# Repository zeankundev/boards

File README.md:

# zeankun.dev's KiCad Boards Repository
A collection of folders for all of my KiCad projects. Archived projects also go here. Go take a look if you want to explore

## Prerequisite
You will need:
- KiCad 8.0 (do not use nightly builds) or later
- git

Just clone the repo. That's it.
```
git clone https://github.com/zeankundev/boards.git
```

## Directory explanation
Most of the projects you see here often orientate around microcontrollers. If you want an even more detailed one, you can read the listing here.

- `Pico2040` and `Pico2350` series. These are my self-designed boards oriented mostly around ARM microcontrollers. especially the RP2040 and the RP2350
- `LiPower`, `BreadPower` and `LCDRucksack`. Those are two board categories that I like to classify them as being "useless". LiPower being the overengineered version of the TP4056 charger, BreadPower being the most **generic** breadboard power supply. Of course, this was designed before I even know USB-C PD. LCDRucksack is just literally a clone of the LCD backpacks out there, but with castellated holes.
- `ProyekOPSI2023` was the board I designed for the Indonesian research competition OPSI, in which I participated. There are two variants; the main is one contains an integrated MCU, being the ATMega328P, while the other one requires you to solder on a Pico2040 R2 Wireless by yourself.

Have fun, LOL. Dig in on my archive. I might try to update more if I have a board to design. Anyways, cya.

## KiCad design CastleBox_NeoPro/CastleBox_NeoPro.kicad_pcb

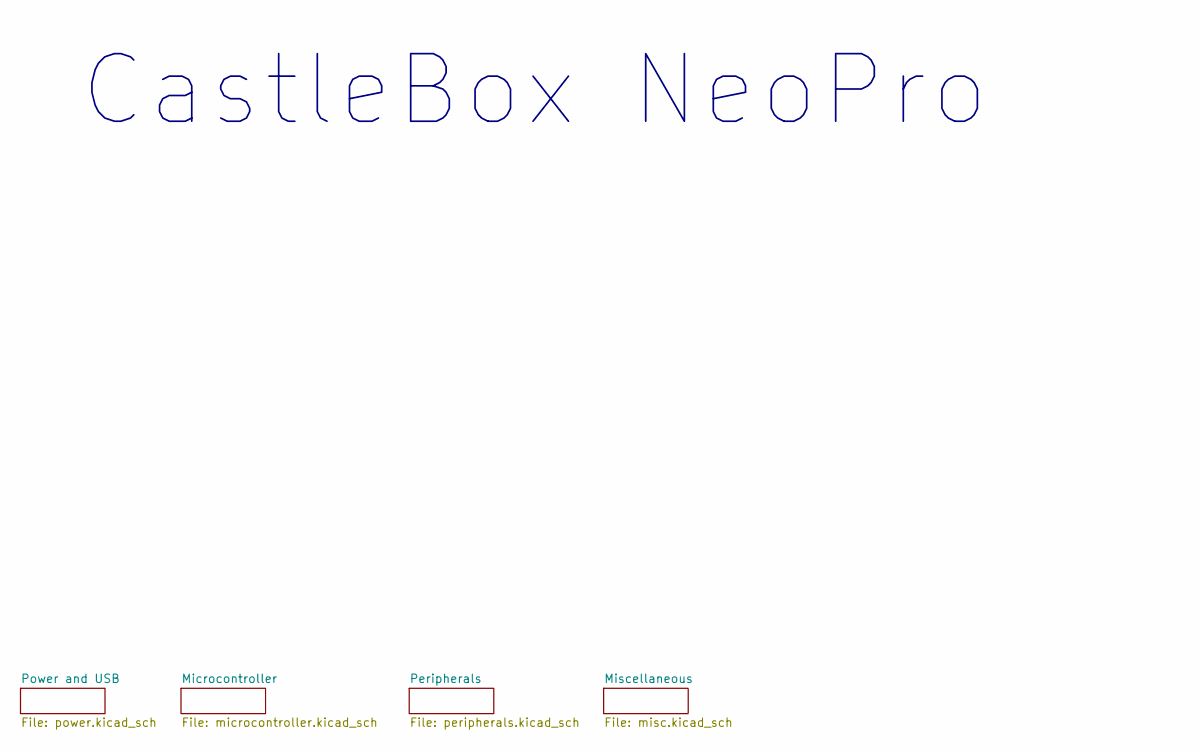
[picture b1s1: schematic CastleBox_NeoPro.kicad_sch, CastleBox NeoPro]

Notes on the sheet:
CastleBox NeoPro

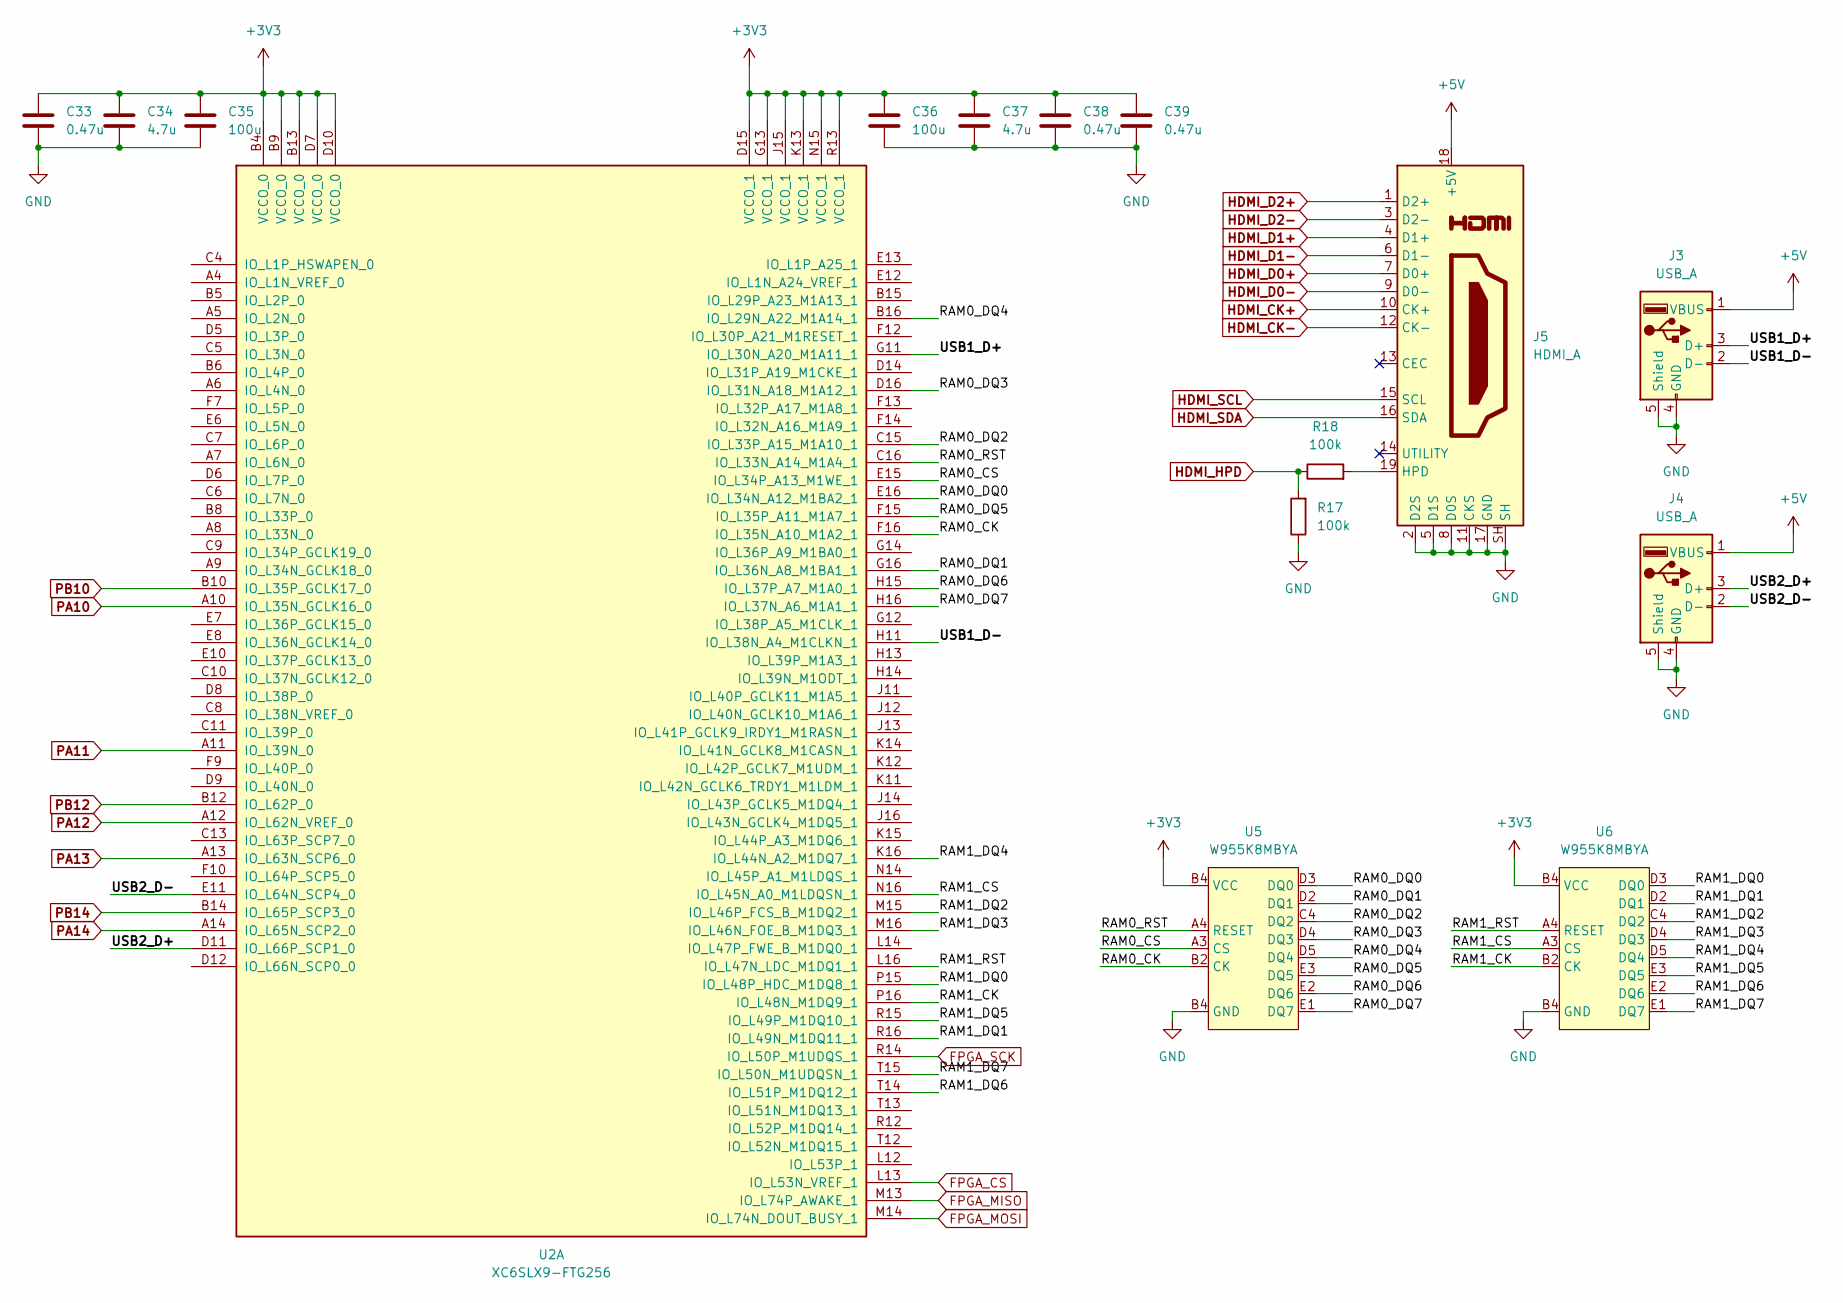
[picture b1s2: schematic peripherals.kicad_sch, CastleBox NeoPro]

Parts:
C33, C38, C39: 0.47u; C_0402_1005Metric
C34, C37: 4.7u; C_0402_1005Metric
C35, C36: 100u; C_0402_1005Metric
J3, J4: USB_A; USB_A_Connfly_DS1095
J5: HDMI_A; HDMI_A_Molex_208658-1001_Horizontal
R17, R18: 100k; R_0402_1005Metric
U2: XC6SLX9-FTG256; BGA-256_17.0x17.0mm_Layout16x16_P1.0mm_Ball0.5mm_Pad0.4mm_N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
U5, U6: W955K8MBYA

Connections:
+5V: J3.1 (VBUS), J4.1 (VBUS), J5.18 (+5V); also elsewhere on the board
/Peripherals/RAM0_CK: U2.F16 (IO_L35N_A10_M1A2_1), U5.B2 (CK)
/Peripherals/RAM0_CS: U2.E15 (IO_L34P_A13_M1WE_1), U5.A3 (CS)
/Peripherals/RAM0_DQ0: U2.E16 (IO_L34N_A12_M1BA2_1), U5.D3 (DQ0)
/Peripherals/RAM0_DQ1: U2.G16 (IO_L36N_A8_M1BA1_1), U5.D2 (DQ1)
/Peripherals/RAM0_DQ2: U2.C15 (IO_L33P_A15_M1A10_1), U5.C4 (DQ2)
/Peripherals/RAM0_DQ3: U2.D16 (IO_L31N_A18_M1A12_1), U5.D4 (DQ3)
/Peripherals/RAM0_DQ4: U2.B16 (IO_L29N_A22_M1A14_1), U5.D5 (DQ4)
/Peripherals/RAM0_DQ5: U2.F15 (IO_L35P_A11_M1A7_1), U5.E3 (DQ5)
/Peripherals/RAM0_DQ6: U2.H15 (IO_L37P_A7_M1A0_1), U5.E2 (DQ6)
/Peripherals/RAM0_DQ7: U2.H16 (IO_L37N_A6_M1A1_1), U5.E1 (DQ7)
/Peripherals/RAM0_RST: U2.C16 (IO_L33N_A14_M1A4_1), U5.A4 (RESET)
/Peripherals/RAM1_CK: U2.P16 (IO_L48N_M1DQ9_1), U6.B2 (CK)
/Peripherals/RAM1_CS: U2.N16 (IO_L45N_A0_M1LDQSN_1), U6.A3 (CS)
/Peripherals/RAM1_DQ0: U2.P15 (IO_L48P_HDC_M1DQ8_1), U6.D3 (DQ0)
/Peripherals/RAM1_DQ1: U2.R16 (IO_L49N_M1DQ11_1), U6.D2 (DQ1)
/Peripherals/RAM1_DQ2: U2.M15 (IO_L46P_FCS_B_M1DQ2_1), U6.C4 (DQ2)
/Peripherals/RAM1_DQ3: U2.M16 (IO_L46N_FOE_B_M1DQ3_1), U6.D4 (DQ3)
/Peripherals/RAM1_DQ4: U2.K16 (IO_L44N_A2_M1DQ7_1), U6.D5 (DQ4)
/Peripherals/RAM1_DQ5: U2.R15 (IO_L49P_M1DQ10_1), U6.E3 (DQ5)
/Peripherals/RAM1_DQ6: U2.T14 (IO_L51P_M1DQ12_1), U6.E2 (DQ6)
/Peripherals/RAM1_DQ7: U2.T15 (IO_L50N_M1UDQSN_1), U6.E1 (DQ7)
/Peripherals/RAM1_RST: U2.L16 (IO_L47N_LDC_M1DQ1_1), U6.A4 (RESET)
/Peripherals/USB1_D+: J3.3 (D+), U2.G11 (IO_L30N_A20_M1A11_1)
/Peripherals/USB1_D-: J3.2 (D-), U2.H11 (IO_L38N_A4_M1CLKN_1)
/Peripherals/USB2_D+: J4.3 (D+), U2.D11 (IO_L66P_SCP1_0)
/Peripherals/USB2_D-: J4.2 (D-), U2.E11 (IO_L64N_SCP4_0)
FPGA_CS: U2.L13 (IO_L53N_VREF_1); also elsewhere on the board
FPGA_MISO: U2.M13 (IO_L74P_AWAKE_1); also elsewhere on the board
FPGA_MOSI: U2.M14 (IO_L74N_DOUT_BUSY_1); also elsewhere on the board
FPGA_SCK: U2.R14 (IO_L50P_M1UDQS_1); also elsewhere on the board
HDMI_CK+: J5.10 (CK+); also elsewhere on the board
HDMI_CK-: J5.12 (CK-); also elsewhere on the board
HDMI_D0+: J5.7 (D0+); also elsewhere on the board
HDMI_D0-: J5.9 (D0-); also elsewhere on the board
HDMI_D1+: J5.4 (D1+); also elsewhere on the board
HDMI_D1-: J5.6 (D1-); also elsewhere on the board
HDMI_D2+: J5.1 (D2+); also elsewhere on the board
HDMI_D2-: J5.3 (D2-); also elsewhere on the board
HDMI_HPD: R17.2, R18.1; also elsewhere on the board
HDMI_SCL: J5.15 (SCL); also elsewhere on the board
HDMI_SDA: J5.16 (SDA); also elsewhere on the board
unnamed: J5.19 (HPD), R18.2
PA10: U2.A10 (IO_L35N_GCLK16_0); also elsewhere on the board
PA11: U2.A11 (IO_L39N_0); also elsewhere on the board
PA12: U2.A12 (IO_L62N_VREF_0); also elsewhere on the board
PA13: U2.A13 (IO_L63N_SCP6_0); also elsewhere on the board
PA14: U2.A14 (IO_L65N_SCP2_0); also elsewhere on the board
PB10: U2.B10 (IO_L35P_GCLK17_0); also elsewhere on the board
PB12: U2.B12 (IO_L62P_0); also elsewhere on the board
PB14: U2.B14 (IO_L65P_SCP3_0); also elsewhere on the board

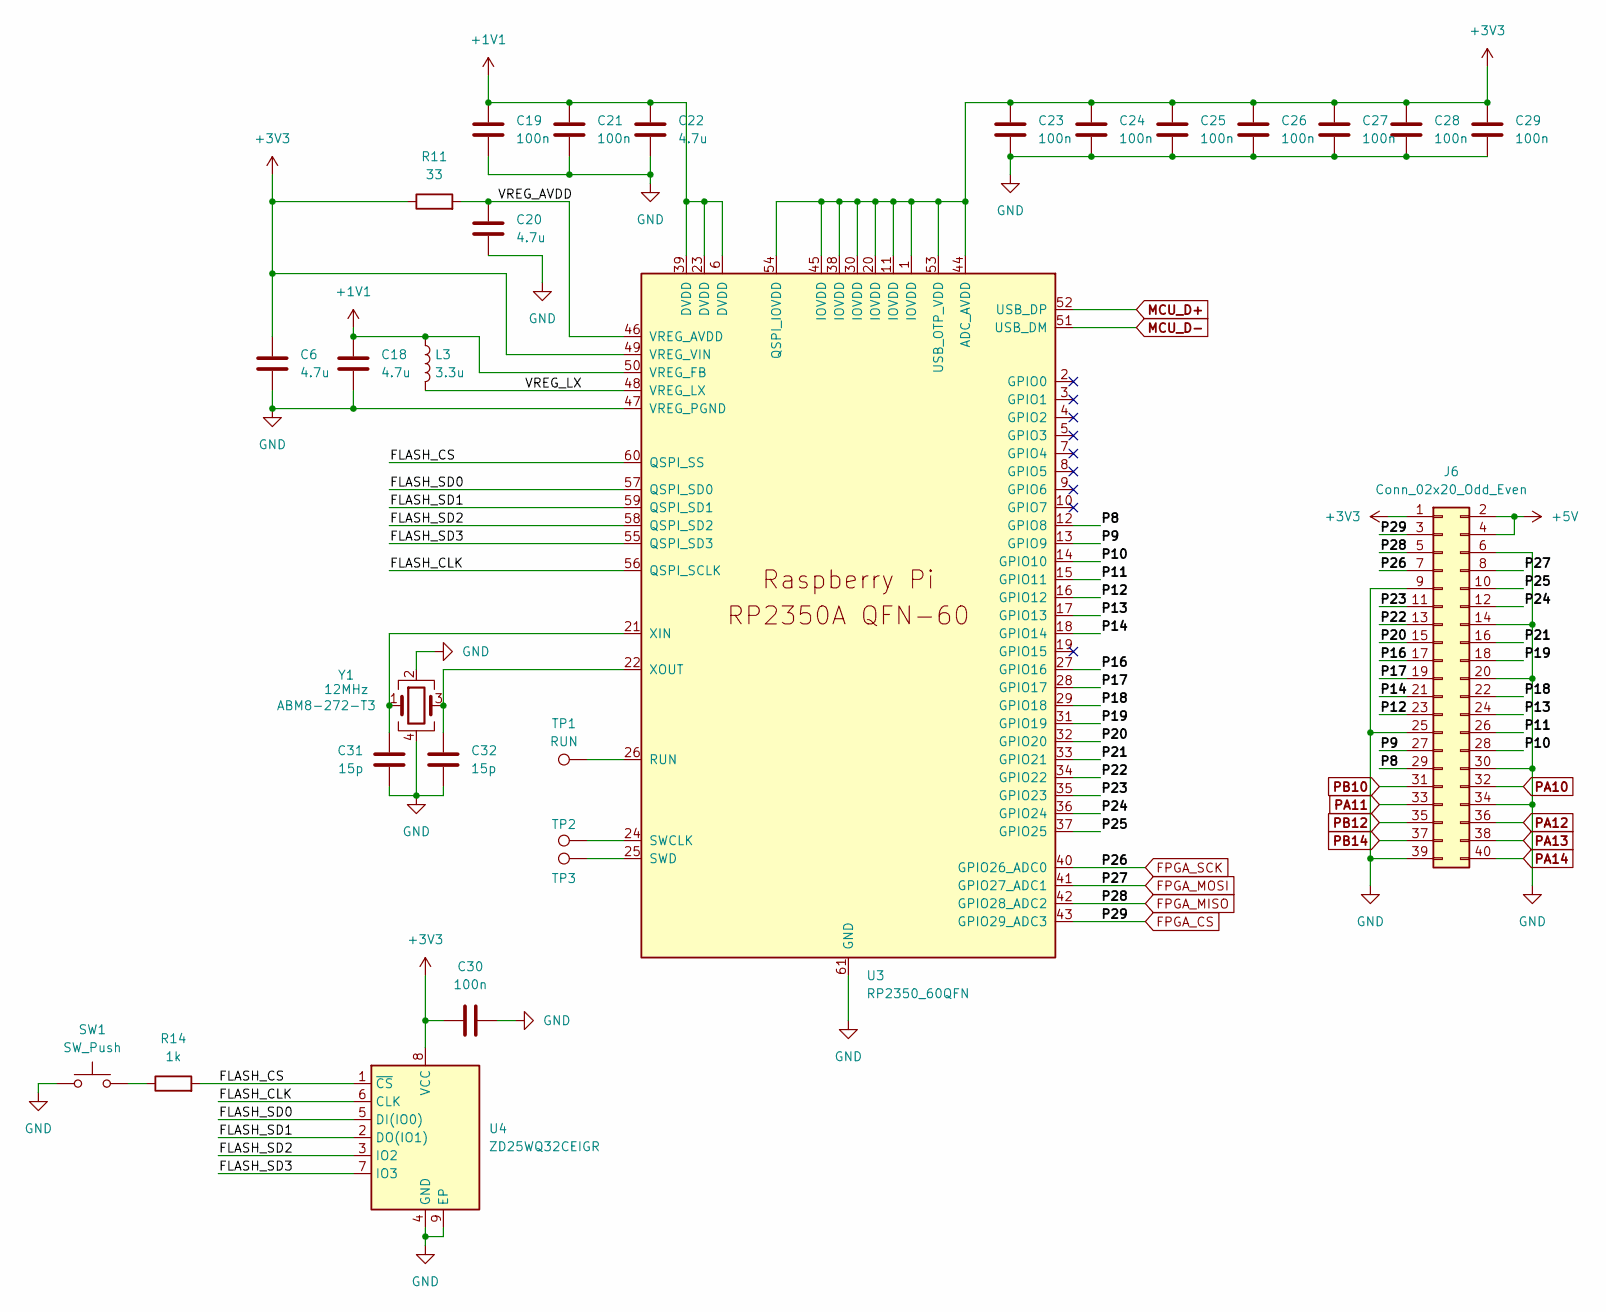
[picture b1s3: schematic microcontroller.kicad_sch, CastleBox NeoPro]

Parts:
C6, C18, C20, C22: 4.7u; C_0402_1005Metric
C19, C21, C23, C24, C25, C26, C27, C28, C29, C30: 100n; C_0402_1005Metric
C31, C32: 15p; C_0402_1005Metric
J6: Conn_02x20_Odd_Even; PinHeader_2x20_P2.54mm_Vertical
L3: 3.3u; L_pol_2016
R11: 33; R_0402_1005Metric
R14: 1k; R_0402_1005Metric
SW1: SW_Push; SW_Push_1P1T_NO_Vertical_Wuerth_434133025816
TP1: RUN; TestPoint_Pad_D1.0mm
TP2, TP3: TestPoint; TestPoint_Pad_D1.0mm
U3: RP2350_60QFN; RP2350-QFN-60-1EP_7x7_P0.4mm_EP3.4x3.4mm_ThermalVias
U4: ZD25WQ32CEIGR; Winbond_USON-8-1EP_3x2mm_P0.5mm_EP0.2x1.6mm
Y1: 12MHz; Crystal_SMD_3225-4Pin_3.2x2.5mm

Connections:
+1V1: C18.1, C19.1, C21.1, C22.1, L3.1, U3.6 (DVDD), U3.23 (DVDD), U3.39 (DVDD), U3.50 (VREG_FB)
+5V: J6.2, J6.4; also elsewhere on the board
/Microcontroller/FLASH_CLK: U3.56 (QSPI_SCLK), U4.6 (CLK)
/Microcontroller/FLASH_CS: R14.2, U3.60 (QSPI_SS), U4.1 (~CS)
/Microcontroller/FLASH_SD0: U3.57 (QSPI_SD0), U4.5 (DI(IO0))
/Microcontroller/FLASH_SD1: U3.59 (QSPI_SD1), U4.2 (DO(IO1))
/Microcontroller/FLASH_SD2: U3.58 (QSPI_SD2), U4.3 (IO2)
/Microcontroller/FLASH_SD3: U3.55 (QSPI_SD3), U4.7 (IO3)
/Microcontroller/P8: J6.29, U3.12 (GPIO8)
/Microcontroller/P9: J6.27, U3.13 (GPIO9)
/Microcontroller/P10: J6.28, U3.14 (GPIO10)
/Microcontroller/P11: J6.26, U3.15 (GPIO11)
/Microcontroller/P12: J6.23, U3.16 (GPIO12)
/Microcontroller/P13: J6.24, U3.17 (GPIO13)
/Microcontroller/P14: J6.21, U3.18 (GPIO14)
/Microcontroller/P16: J6.17, U3.27 (GPIO16)
/Microcontroller/P17: J6.19, U3.28 (GPIO17)
/Microcontroller/P18: J6.22, U3.29 (GPIO18)
/Microcontroller/P19: J6.18, U3.31 (GPIO19)
/Microcontroller/P20: J6.15, U3.32 (GPIO20)
/Microcontroller/P21: J6.16, U3.33 (GPIO21)
/Microcontroller/P22: J6.13, U3.34 (GPIO22)
/Microcontroller/P23: J6.11, U3.35 (GPIO23)
/Microcontroller/P24: J6.12, U3.36 (GPIO24)
/Microcontroller/P25: J6.10, U3.37 (GPIO25)
/Microcontroller/VREG_AVDD: C20.1, R11.2, U3.46 (VREG_AVDD)
/Microcontroller/VREG_LX: L3.2, U3.48 (VREG_LX)
FPGA_CS: J6.3, U3.43 (GPIO29_ADC3); also elsewhere on the board
FPGA_MISO: J6.5, U3.42 (GPIO28_ADC2); also elsewhere on the board
FPGA_MOSI: J6.8, U3.41 (GPIO27_ADC1); also elsewhere on the board
FPGA_SCK: J6.7, U3.40 (GPIO26_ADC0); also elsewhere on the board
MCU_D+: U3.52 (USB_DP); also elsewhere on the board
MCU_D-: U3.51 (USB_DM); also elsewhere on the board
unnamed: R14.1, SW1.2
unnamed: TP1.1, U3.26 (RUN)
unnamed: TP2.1, U3.24 (SWCLK)
unnamed: TP3.1, U3.25 (SWD)
unnamed: C31.1, U3.21 (XIN), Y1.1
unnamed: C32.1, U3.22 (XOUT), Y1.3
PA10: J6.32; also elsewhere on the board
PA11: J6.33; also elsewhere on the board
PA12: J6.36; also elsewhere on the board
PA13: J6.38; also elsewhere on the board
PA14: J6.40; also elsewhere on the board
PB10: J6.31; also elsewhere on the board
PB12: J6.35; also elsewhere on the board
PB14: J6.37; also elsewhere on the board

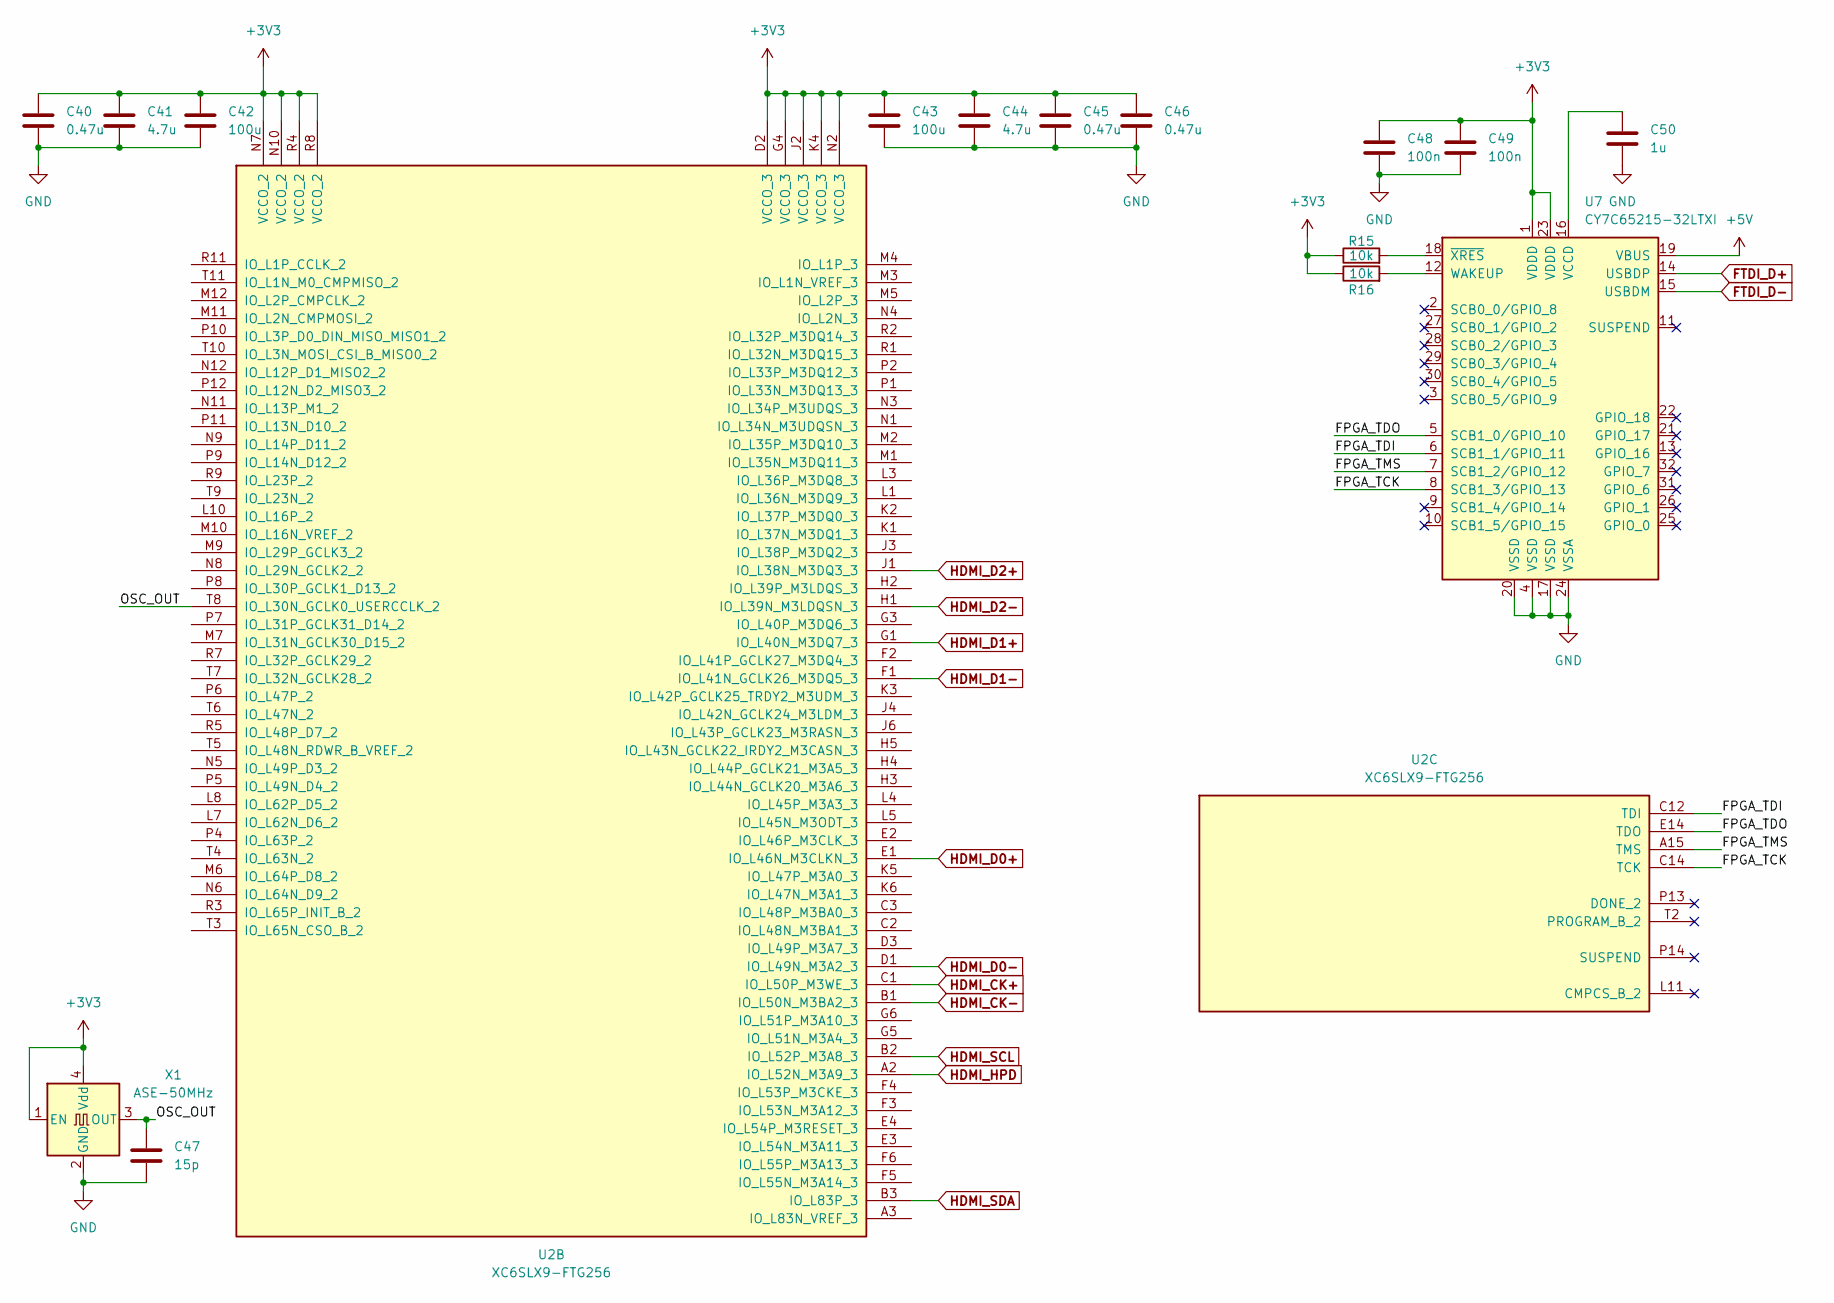
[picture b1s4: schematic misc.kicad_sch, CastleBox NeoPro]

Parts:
C40, C45, C46: 0.47u; C_0402_1005Metric
C41, C44: 4.7u; C_0402_1005Metric
C42, C43: 100u; C_0402_1005Metric
C47: 15p; C_0402_1005Metric
C48, C49: 100n; C_0402_1005Metric
C50: 1u; C_0402_1005Metric
R15, R16: 10k; R_0402_1005Metric
U2: XC6SLX9-FTG256
U7: CY7C65215-32LTXI; QFN-32-1EP_5x5mm_P0.5mm_EP3.45x3.45mm
X1: ASE-50MHz; Oscillator_SMD_Abracon_ASE-4Pin_3.2x2.5mm

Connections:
+5V: U7.19 (VBUS); also elsewhere on the board
/Miscellaneous/FPGA_TCK: U2.C14 (TCK), U7.8 (SCB1_3/GPIO_13)
/Miscellaneous/FPGA_TDI: U2.C12 (TDI), U7.6 (SCB1_1/GPIO_11)
/Miscellaneous/FPGA_TDO: U2.E14 (TDO), U7.5 (SCB1_0/GPIO_10)
/Miscellaneous/FPGA_TMS: U2.A15 (TMS), U7.7 (SCB1_2/GPIO_12)
/Miscellaneous/OSC_OUT: C47.1, U2.T8 (IO_L30N_GCLK0_USERCCLK_2), X1.3 (OUT)
FTDI_D+: U7.14 (USBDP); also elsewhere on the board
FTDI_D-: U7.15 (USBDM); also elsewhere on the board
HDMI_CK+: U2.C1 (IO_L50P_M3WE_3); also elsewhere on the board
HDMI_CK-: U2.B1 (IO_L50N_M3BA2_3); also elsewhere on the board
HDMI_D0+: U2.E1 (IO_L46N_M3CLKN_3); also elsewhere on the board
HDMI_D0-: U2.D1 (IO_L49N_M3A2_3); also elsewhere on the board
HDMI_D1+: U2.G1 (IO_L40N_M3DQ7_3); also elsewhere on the board
HDMI_D1-: U2.F1 (IO_L41N_GCLK26_M3DQ5_3); also elsewhere on the board
HDMI_D2+: U2.J1 (IO_L38N_M3DQ3_3); also elsewhere on the board
HDMI_D2-: U2.H1 (IO_L39N_M3LDQSN_3); also elsewhere on the board
HDMI_HPD: U2.A2 (IO_L52N_M3A9_3); also elsewhere on the board
HDMI_SCL: U2.B2 (IO_L52P_M3A8_3); also elsewhere on the board
HDMI_SDA: U2.B3 (IO_L83P_3); also elsewhere on the board
unnamed: C50.1, U7.16 (VCCD)
unnamed: R16.2, U7.12 (WAKEUP)
unnamed: R15.2, U7.18 (~XRES)

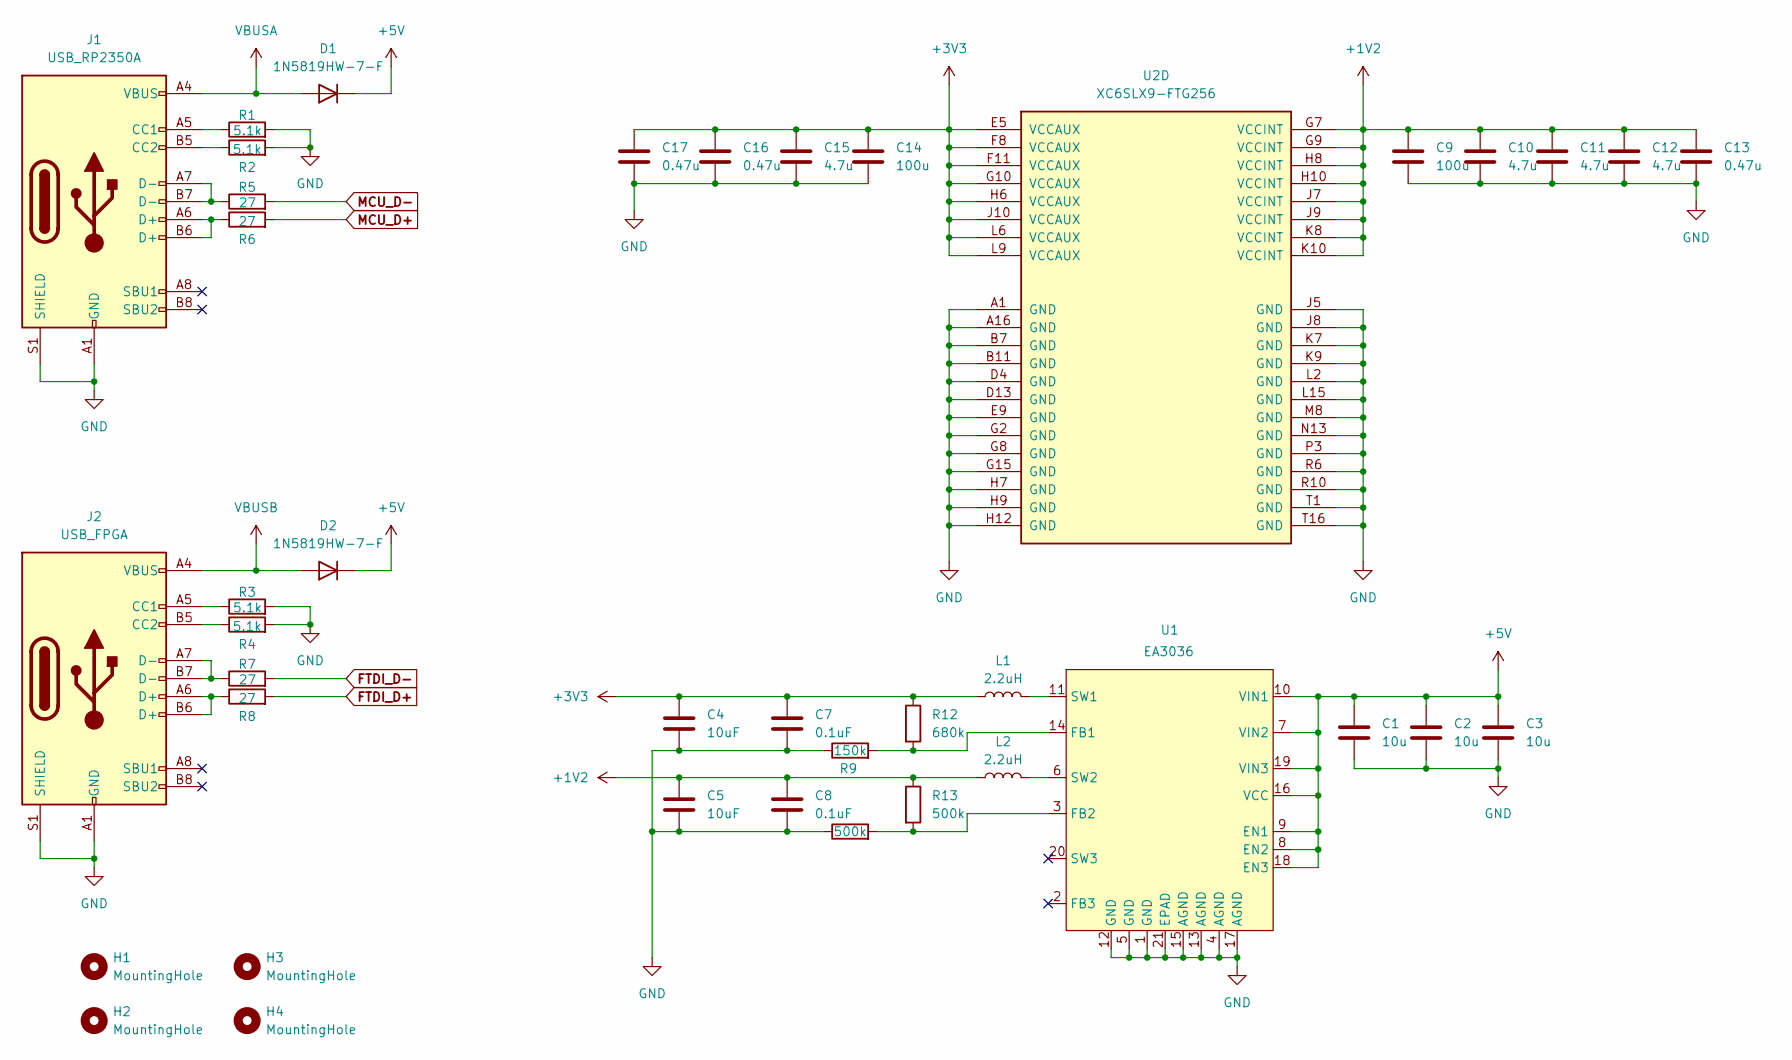
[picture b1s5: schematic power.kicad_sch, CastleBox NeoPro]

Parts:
C1, C2, C3: 10u; C_0402_1005Metric
C4, C5: 10uF; C_0402_1005Metric
C7, C8: 0.1uF; C_0402_1005Metric
C9, C14: 100u; C_0402_1005Metric
C10, C11, C12, C15: 4.7u; C_0402_1005Metric
C13, C16, C17: 0.47u; C_0402_1005Metric
D1, D2: 1N5819HW-7-F; D_SOD-123
H1, H2, H3, H4: MountingHole; MountingHole_2.5mm
J1: USB_RP2350A; USB_C_Receptacle_GCT_USB4105-xx-A_16P_TopMnt_Horizontal
J2: USB_FPGA; USB_C_Receptacle_GCT_USB4105-xx-A_16P_TopMnt_Horizontal
L1, L2: 2.2uH; L_Changjiang_FNR252010S
R1, R2, R3, R4: 5.1k; R_0402_1005Metric
R5, R6, R7, R8: 27; R_0402_1005Metric
R9: 150k; R_0402_1005Metric
R10, R13: 500k; R_0402_1005Metric
R12: 680k; R_0402_1005Metric
U1: EA3036; WQFN-20-1EP_3x3mm_P0.4mm_EP1.7x1.7mm_ThermalVias
U2: XC6SLX9-FTG256; BGA-256_17.0x17.0mm_Layout16x16_P1.0mm_Ball0.5mm_Pad0.4mm_N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

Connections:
+1V2: C5.1, C8.1, C9.1, C10.1, C11.1, C12.1, C13.1, L2.1, R13.1, U2.G7 (VCCINT), U2.G9 (VCCINT), U2.H8 (VCCINT), U2.H10 (VCCINT), U2.J7 (VCCINT), U2.J9 (VCCINT), U2.K8 (VCCINT), U2.K10 (VCCINT)
+5V: C1.1, C2.1, C3.1, D1.1 (K), D2.1 (K), U1.7 (VIN2), U1.8 (EN2), U1.9 (EN1), U1.10 (VIN1), U1.16 (VCC), U1.18 (EN3), U1.19 (VIN3); also elsewhere on the board
FTDI_D+: R8.2; also elsewhere on the board
FTDI_D-: R7.2; also elsewhere on the board
MCU_D+: R6.2; also elsewhere on the board
MCU_D-: R5.2; also elsewhere on the board
unnamed: J1.A5 (CC1), R1.1
unnamed: J1.B5 (CC2), R2.1
unnamed: J1.A6 (D+), J1.B6 (D+), R6.1
unnamed: J1.A7 (D-), J1.B7 (D-), R5.1
unnamed: J2.A5 (CC1), R3.1
unnamed: J2.B5 (CC2), R4.1
unnamed: J2.A6 (D+), J2.B6 (D+), R8.1
unnamed: J2.A7 (D-), J2.B7 (D-), R7.1
unnamed: R9.2, R12.2, U1.14 (FB1)
unnamed: R10.2, R13.2, U1.3 (FB2)
unnamed: L1.2, U1.11 (SW1)
unnamed: L2.2, U1.6 (SW2)
VBUSA: D1.2 (A), J1.A4 (VBUS), J1.A9 (VBUS), J1.B4 (VBUS), J1.B9 (VBUS)
VBUSB: D2.2 (A), J2.A4 (VBUS), J2.A9 (VBUS), J2.B4 (VBUS), J2.B9 (VBUS)

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
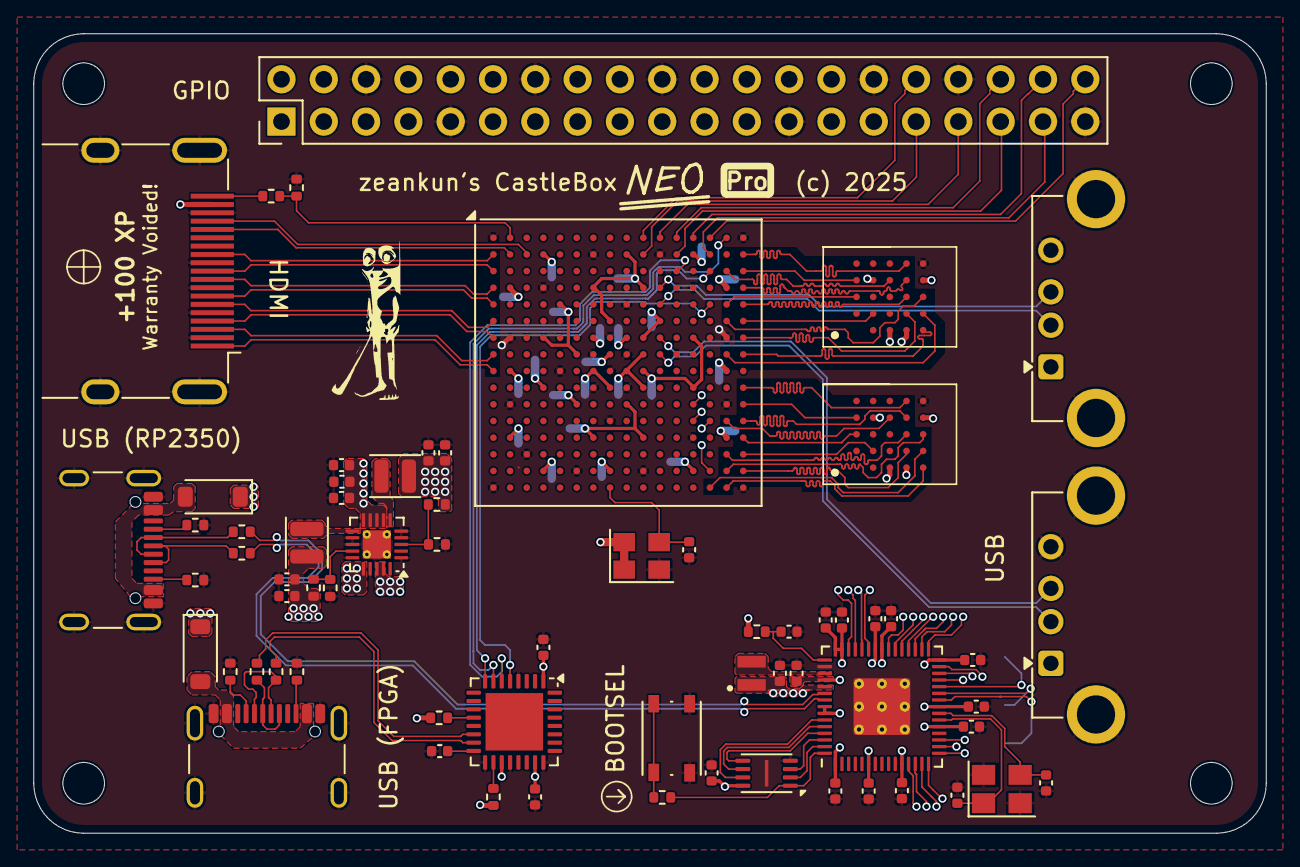
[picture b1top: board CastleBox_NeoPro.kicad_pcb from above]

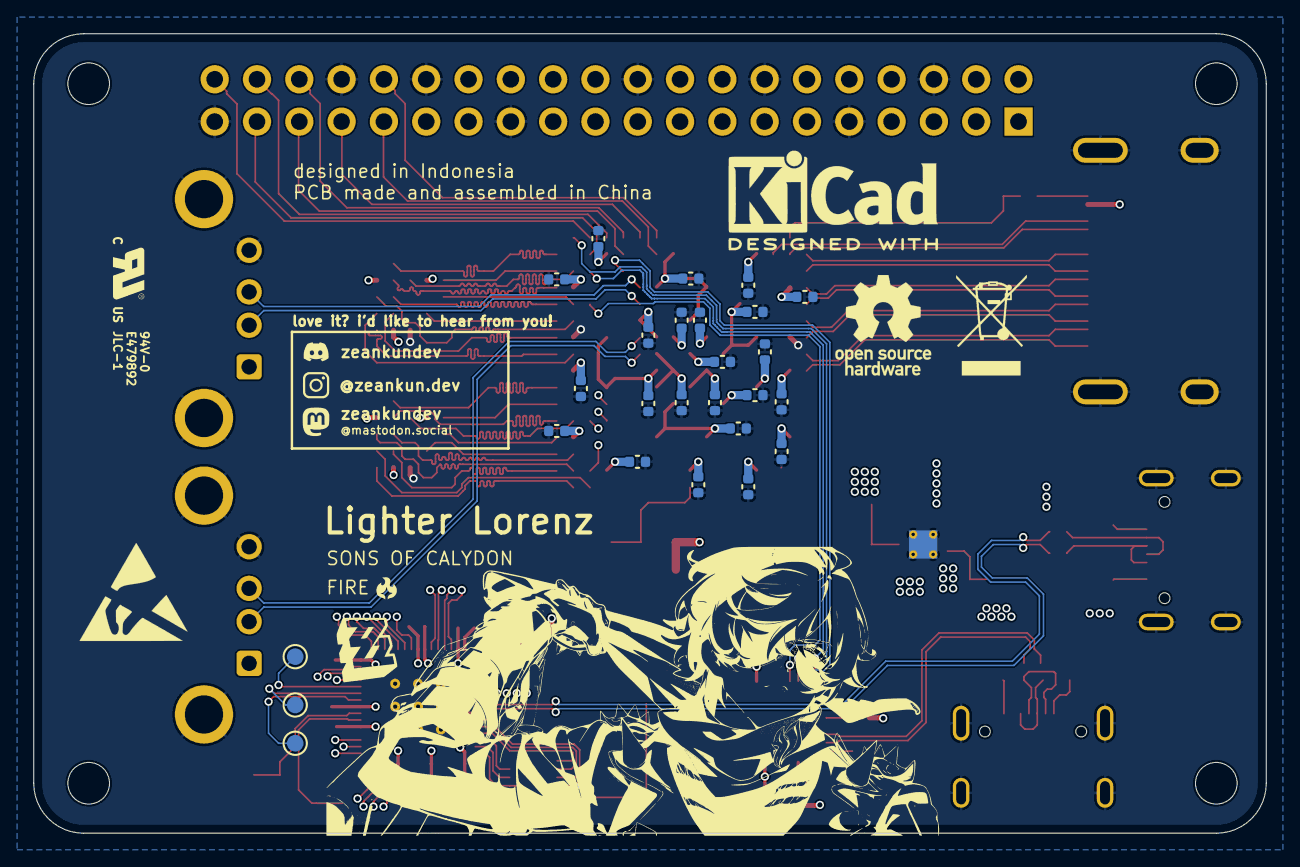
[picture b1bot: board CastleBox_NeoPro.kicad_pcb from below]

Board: 4 copper layers, 74.0 x 48.0 mm, 96 parts (26 on the bottom side), 112 nets.

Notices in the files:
CastleBox/CastleBox.kicad_pcb:
©️ 2025 zeankun.dev.
logo ©️ choco panda kat
all rights reserved
CastleBox_NeoPro/CastleBox_NeoPro.kicad_pcb:
(c) 2025
CastleBox_Pro/CastleBox_Pro.kicad_pcb:
© 2025
Keypocket/Keypocket.kicad_pcb:
(logo © 2024)
Pico2040-Rev4/Pico2040-Rev4.kicad_pcb:
zeankun.dev's Pico2040 R4 ©️ 2024
licensed by Book's
©️ 2024 zeankun.dev.
Pico2350-W-R1-LightningEdition/Pico2350-W-R1.kicad_sch:
Copyright (c) 2024 zeankun.dev
Pico2350-W-R1/Pico2350-W-R1.kicad_pcb:
zeankun.dev's Pico2350 W © 2024
